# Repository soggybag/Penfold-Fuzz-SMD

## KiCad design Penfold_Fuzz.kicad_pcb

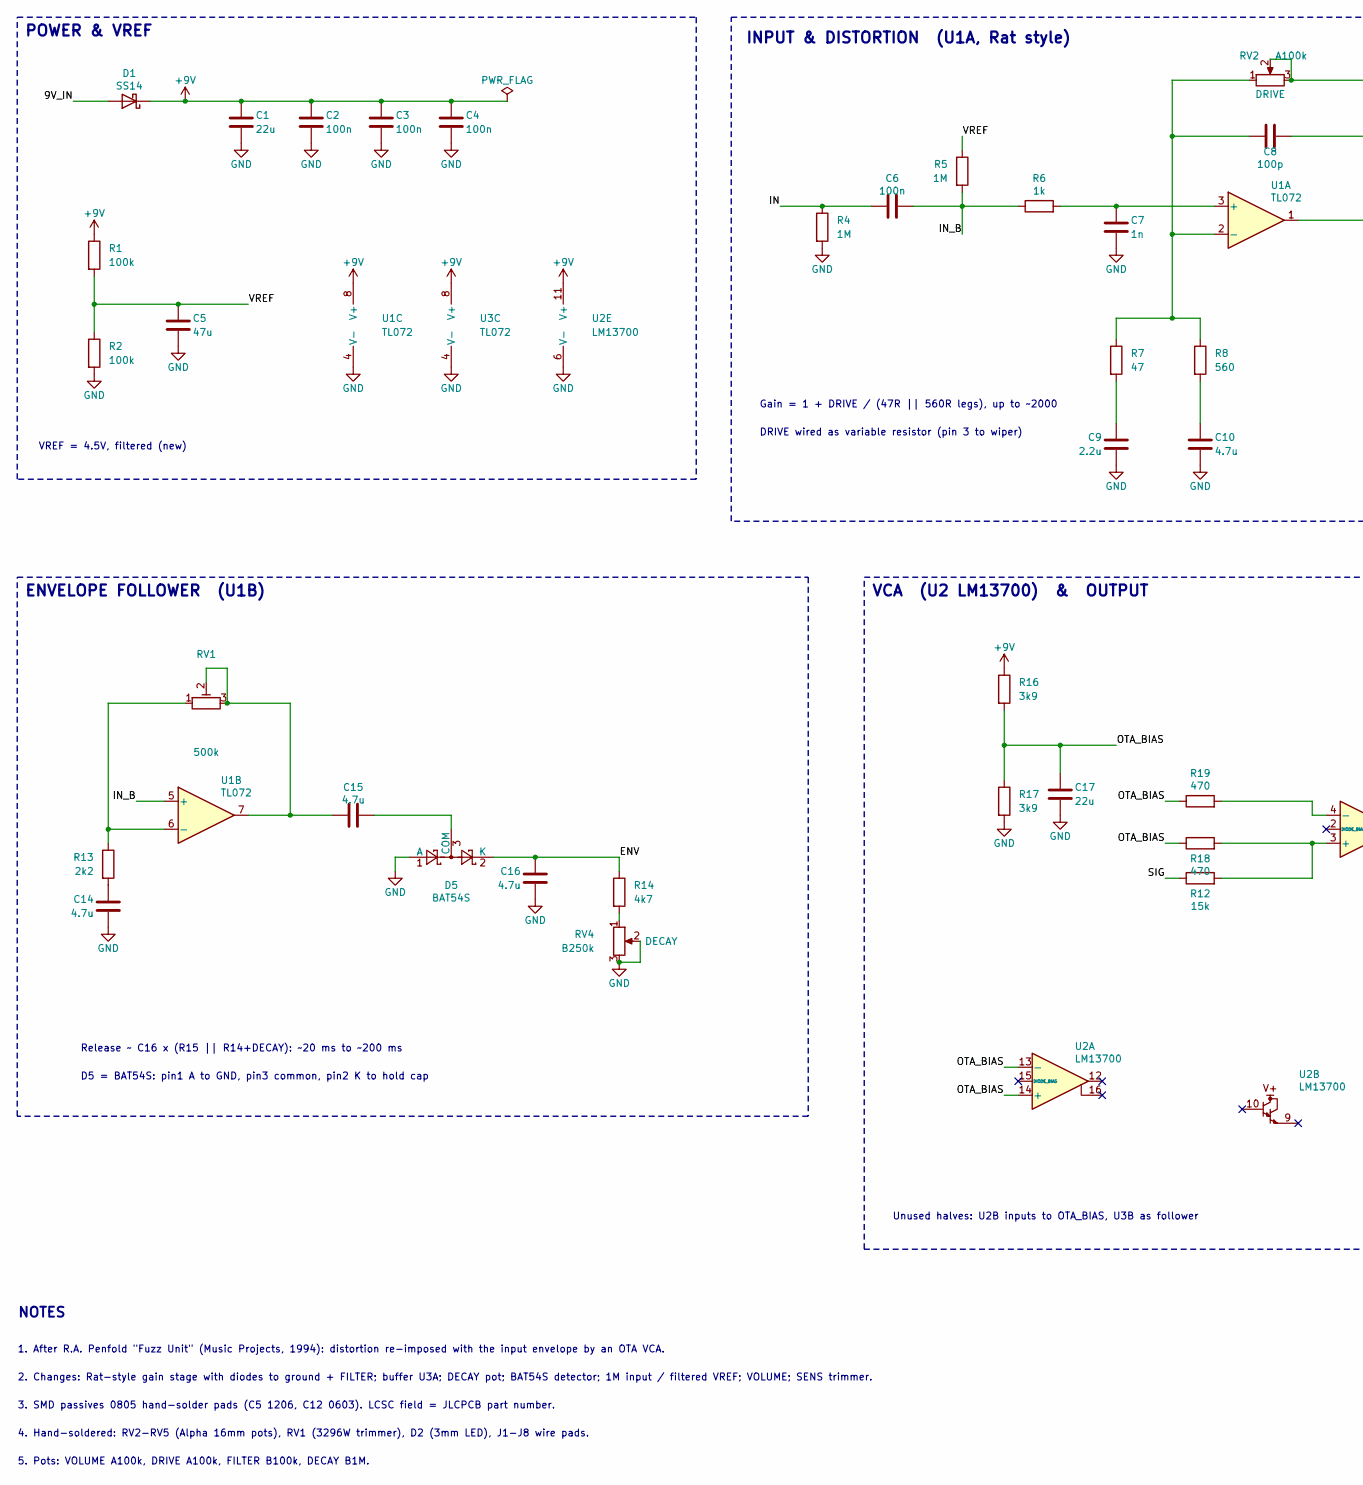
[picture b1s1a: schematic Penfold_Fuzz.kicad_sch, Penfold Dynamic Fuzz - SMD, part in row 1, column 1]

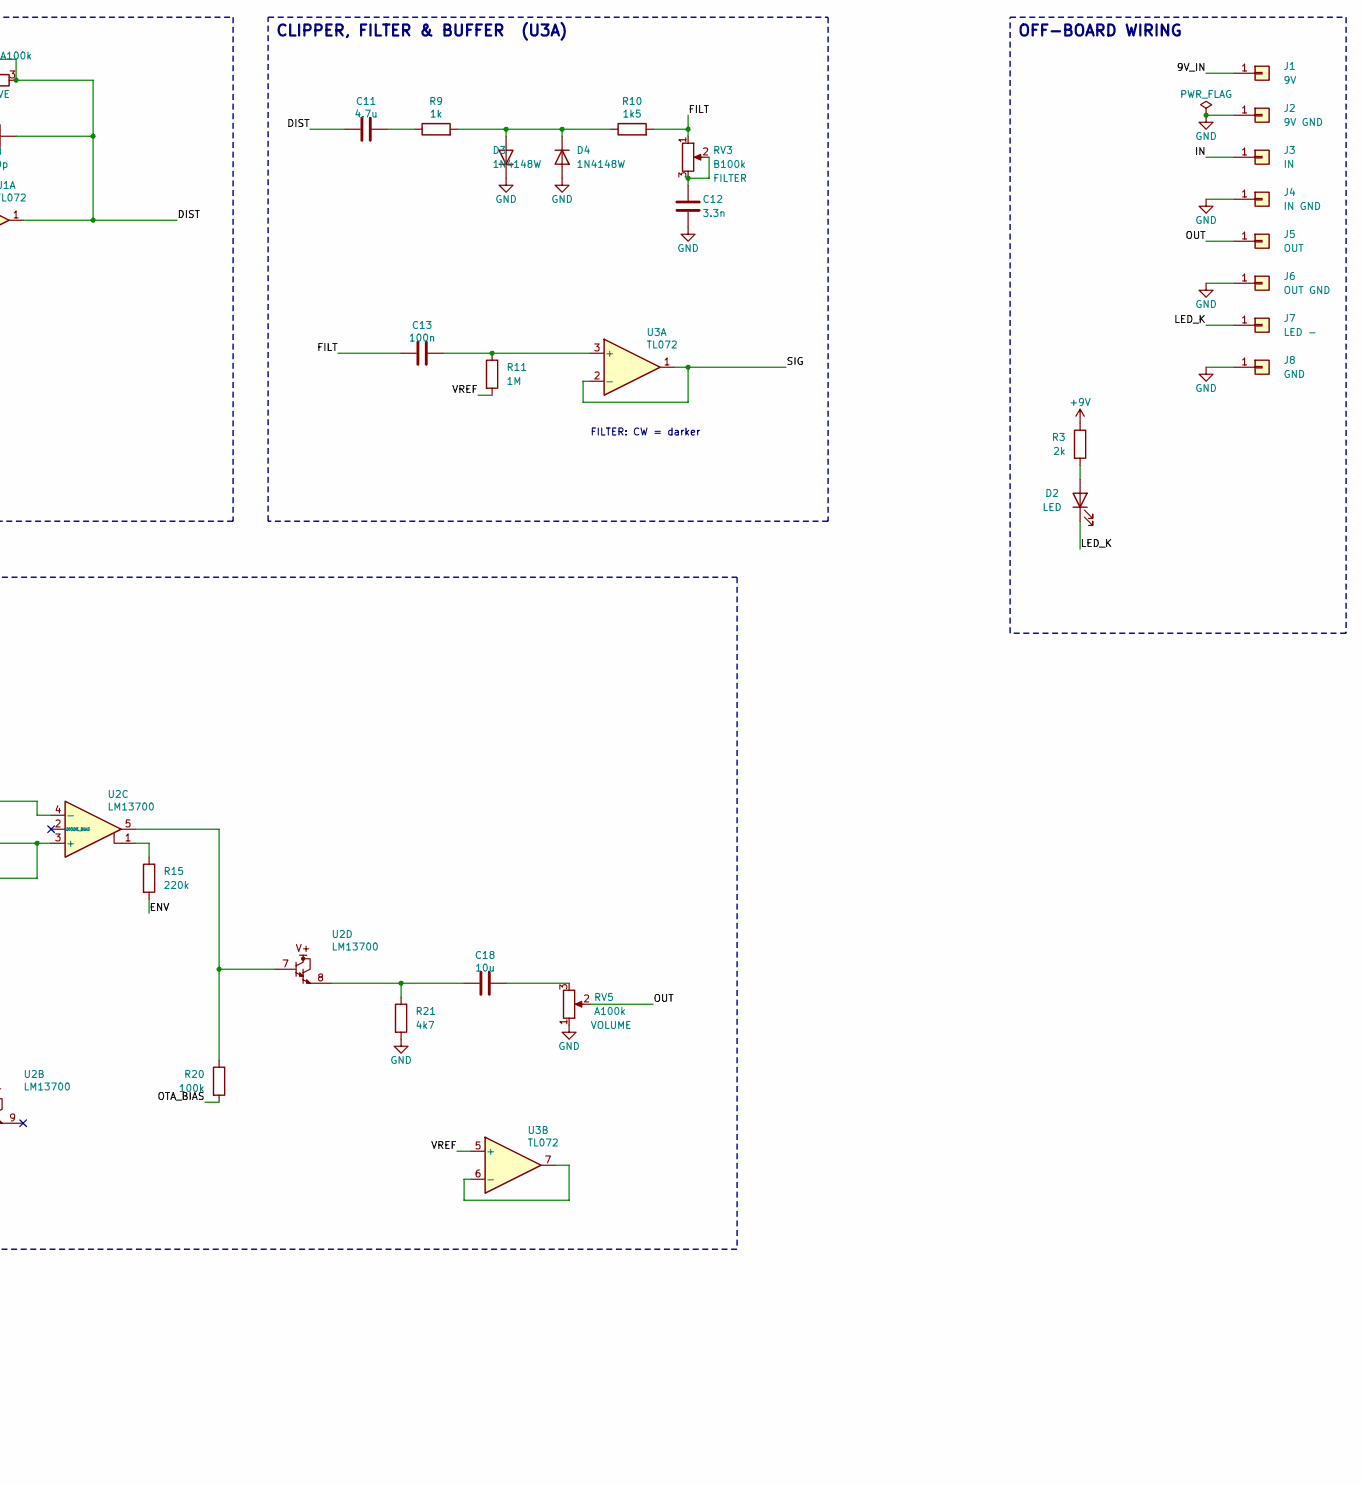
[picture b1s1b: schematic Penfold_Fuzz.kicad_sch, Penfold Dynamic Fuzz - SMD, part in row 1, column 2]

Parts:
C1, C17: 22u; C_0805_2012Metric_Pad1.18x1.45mm_HandSolder; LCSC C45783
C2, C3, C4, C6, C13: 100n; C_0805_2012Metric_Pad1.18x1.45mm_HandSolder; LCSC C49678
C5: 47u; C_1206_3216Metric_Pad1.33x1.80mm_HandSolder; LCSC C96123
C7: 1n; C_0805_2012Metric_Pad1.18x1.45mm_HandSolder; LCSC C46653
C8: 100p; C_0805_2012Metric_Pad1.18x1.45mm_HandSolder; LCSC C1790
C9: 2.2u; C_0805_2012Metric_Pad1.18x1.45mm_HandSolder; LCSC C377773
C10, C11, C14, C15, C16: 4.7u; C_0805_2012Metric_Pad1.18x1.45mm_HandSolder; LCSC C1779
C12: 3.3n; C_0603_1608Metric_Pad1.08x0.95mm_HandSolder; LCSC C1613
C18: 10u; C_0805_2012Metric_Pad1.18x1.45mm_HandSolder; LCSC C15850
D1: SS14; D_SMA_Handsoldering; LCSC C2480
D2: LED; LED_D3.0mm
D3, D4: 1N4148W; D_SOD-123; LCSC C81598
D5: BAT54S; SOT-23; LCSC C19726
J1: 9V; SolderWire-0.5sqmm_1x01_D0.9mm_OD2.1mm
J2: 9V GND; SolderWire-0.5sqmm_1x01_D0.9mm_OD2.1mm
J3: IN; SolderWire-0.5sqmm_1x01_D0.9mm_OD2.1mm
J4: IN GND; SolderWire-0.5sqmm_1x01_D0.9mm_OD2.1mm
J5: OUT; SolderWire-0.5sqmm_1x01_D0.9mm_OD2.1mm
J6: OUT GND; SolderWire-0.5sqmm_1x01_D0.9mm_OD2.1mm
J7: LED -; SolderWire-0.5sqmm_1x01_D0.9mm_OD2.1mm
J8: GND; SolderWire-0.5sqmm_1x01_D0.9mm_OD2.1mm
R1, R2, R20: 100k; R_0805_2012Metric_Pad1.20x1.40mm_HandSolder; LCSC C149504
R3: 2k; R_0805_2012Metric_Pad1.20x1.40mm_HandSolder; LCSC C17604
R4, R5, R11: 1M; R_0805_2012Metric_Pad1.20x1.40mm_HandSolder; LCSC C17514
R6, R9: 1k; R_0805_2012Metric_Pad1.20x1.40mm_HandSolder; LCSC C17513
R7: 47; R_0805_2012Metric_Pad1.20x1.40mm_HandSolder; LCSC C17714
R8: 560; R_0805_2012Metric_Pad1.20x1.40mm_HandSolder; LCSC C28636
R10: 1k5; R_0805_2012Metric_Pad1.20x1.40mm_HandSolder; LCSC C4310
R12: 15k; R_0805_2012Metric_Pad1.20x1.40mm_HandSolder; LCSC C17475
R13: 2k2; R_0805_2012Metric_Pad1.20x1.40mm_HandSolder; LCSC C17520
R14, R21: 4k7; R_0805_2012Metric_Pad1.20x1.40mm_HandSolder; LCSC C17673
R15: 220k; R_0805_2012Metric_Pad1.20x1.40mm_HandSolder; LCSC C17556
R16, R17: 3k9; R_0805_2012Metric_Pad1.20x1.40mm_HandSolder; LCSC C17614
R18, R19: 470; R_0805_2012Metric_Pad1.20x1.40mm_HandSolder; LCSC C17710
RV1: 500k; Potentiometer_Bourns_3362P_Vertical
RV2, RV5: A100k; Potentiometer_Alpha_16mm_Vertical
RV3: B100k; Potentiometer_Alpha_16mm_Vertical
RV4: B250k; Potentiometer_Alpha_16mm_Vertical
U1, U3: TL072; SOIC-8_3.9x4.9mm_P1.27mm; LCSC C6961
U2: LM13700; SOIC-16_3.9x9.9mm_P1.27mm; LCSC C174050

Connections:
/9V_IN: D1.2 (A), J1.1
/DIST: C8.2, C11.1, RV2.2, RV2.3, U1.1
/ENV: C16.1, D5.2 (K), R14.1, R15.2
/FILT: C13.1, R10.2, RV3.1
/IN: C6.1, J3.1, R4.1
/IN_B: C6.2, R5.2, R6.1, U1.5 (+)
/LED_K: D2.1 (K), J7.1
/OTA_BIAS: C17.1, R16.2, R17.1, R18.1, R19.1, R20.2, U2.13 (-), U2.14 (+)
/OUT: J5.1, RV5.2
/SIG: R12.1, U3.1, U3.2 (-)
/VREF: C5.1, R1.2, R2.1, R5.1, R11.2, U3.5 (+)
unnamed: C9.1, R7.2
unnamed: C10.1, R8.2
unnamed: C11.2, R9.1
unnamed: C12.1, RV3.2, RV3.3
unnamed: C14.1, R13.2
unnamed: C15.1, RV1.2, RV1.3, U1.7
unnamed: C18.1, R21.1, U2.8
unnamed: C18.2, RV5.3
unnamed: D2.2 (A), R3.2
unnamed: D3.2 (A), D4.1 (K), R9.2, R10.1
unnamed: C15.2, D5.3 (COM)
unnamed: R14.2, RV4.1
unnamed: R15.1, U2.1
unnamed: R20.1, U2.5, U2.7
unnamed: C7.1, R6.2, U1.3 (+)
unnamed: C8.1, R7.1, R8.1, RV2.1, U1.2 (-)
unnamed: R13.1, RV1.1, U1.6 (-)
unnamed: R12.2, R18.2, U2.3 (+)
unnamed: R19.2, U2.4 (-)
unnamed: C13.2, R11.1, U3.3 (+)
unnamed: U3.6 (-), U3.7

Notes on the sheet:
ENVELOPE FOLLOWER (U1B)
OFF-BOARD WIRING
D5 = BAT54S: pin1 A to GND, pin3 common, pin2 K to hold cap
INPUT & DISTORTION (U1A, Rat style)
Unused halves: U2B inputs to OTA_BIAS, U3B as follower
VCA (U2 LM13700) & OUTPUT
Gain = 1 + DRIVE / (47R || 560R legs), up to ~2000
Release ~ C16 x (R15 || R14+DECAY): ~20 ms to ~200 ms
VREF = 4.5V, filtered (new)
CLIPPER, FILTER & BUFFER (U3A)
DRIVE wired as variable resistor (pin 3 to wiper)
1. After R.A. Penfold "Fuzz Unit" (Music Projects, 1994): distortion re-imposed with the input envelope by an OTA VCA.
2. Changes: Rat-style gain stage with diodes to ground + FILTER; buffer U3A; DECAY pot; BAT54S detector; 1M input / filtered VREF; VOLUME; SENS trimmer.
4. Hand-soldered: RV2-RV5 (Alpha 16mm pots), RV1 (3296W trimmer), D2 (3mm LED), J1-J8 wire pads.
NOTES
5. Pots: VOLUME A100k, DRIVE A100k, FILTER B100k, DECAY B1M.
POWER & VREF
3. SMD passives 0805 hand-solder pads (C5 1206, C12 0603). LCSC field = JLCPCB part number.
FILTER: CW = darker

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
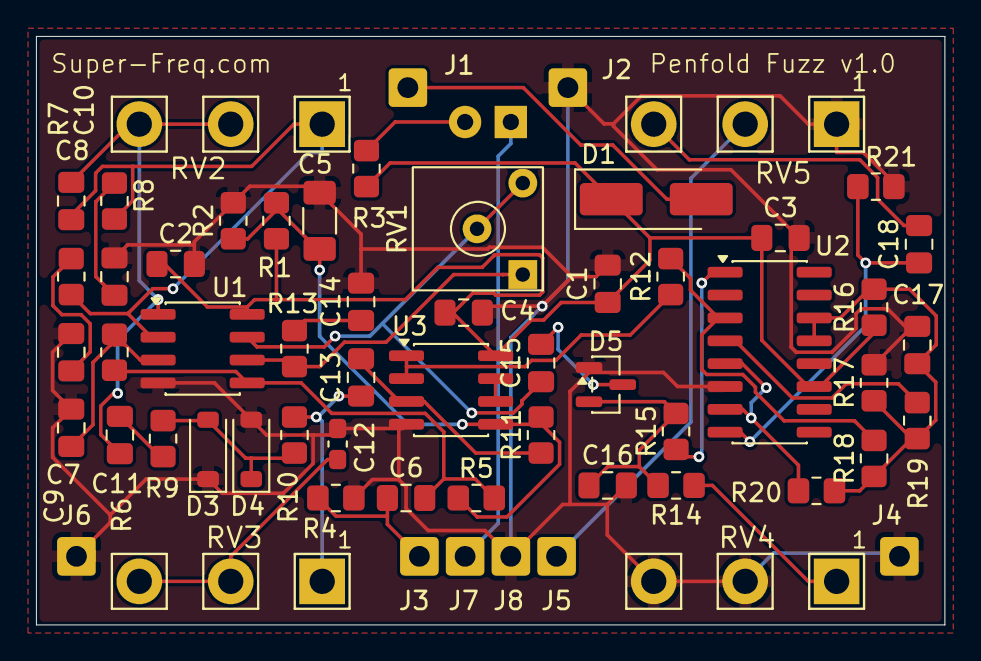
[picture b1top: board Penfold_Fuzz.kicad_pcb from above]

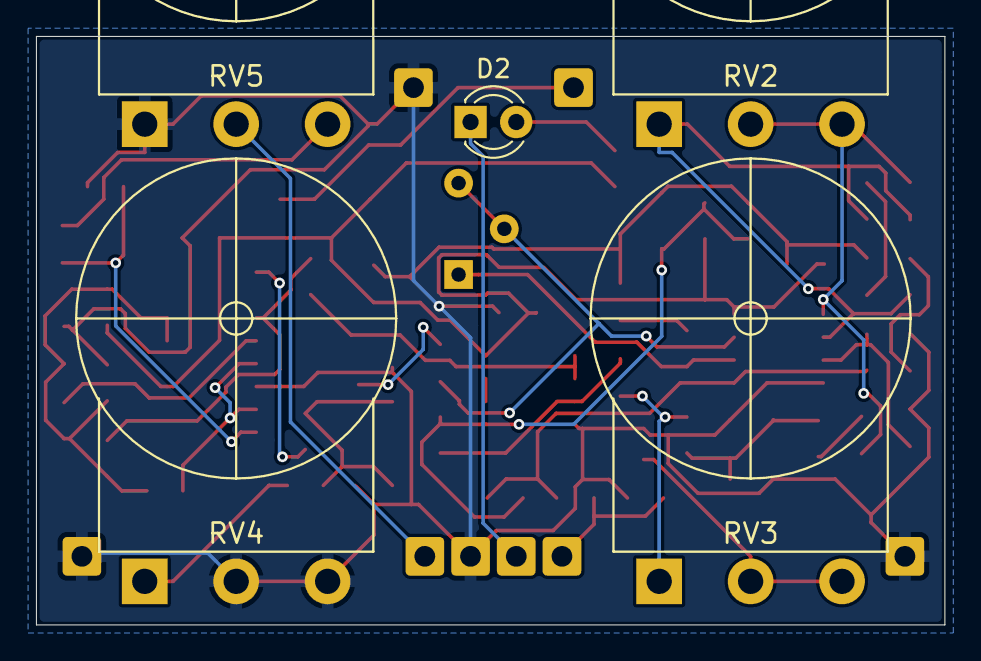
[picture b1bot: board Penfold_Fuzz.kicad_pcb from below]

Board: 2 copper layers, 50.5 x 32.7 mm, 61 parts (2 on the bottom side), 34 nets.

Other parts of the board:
ENC1: Hammond 1590B; Hammond_1590B
